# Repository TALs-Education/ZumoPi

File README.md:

# ZumoPi
ZumoPi is a compact robot platform built around the Pololu Zumo chassis and controlled by a Raspberry Pi. This project is used in various educational settings to demonstrate real-world applications of embedded systems, sensor integration, and autonomous control. The slides below cover topics such as configuring embedded hardware, implementing control loops, and developing path-following algorithms. The goal is to give students hands-on experience with building, programming, and testing autonomous robots.

---

---

## Bill of Materials (BOM)

[BOM ZumoPi V02](https://docs.google.com/spreadsheets/d/e/2PACX-1vQxc54kx69_jDI3SzTPj1htnaY2AYKc5NwDaSZi82ZxfzQ_idLNpaMOl1VLD6l9M_Mb7hPjLyrn291Y/pubhtml)

---

## Course Slides

- **[Autonomous Systems Lab](https://docs.google.com/presentation/d/e/2PACX-1vRStIoiYa2XbYNI_D9ZccQSjIIEqi7QFh0CPTO20TWpKoEXQ6jn_6Y2cxPnYvpHpmra1TaAvrsPDCbp/pub?start=false&loop=false&delayms=60000)**
  *Introduction to building and controlling autonomous robots, covering fundamental concepts such as sensor fusion, actuator control, and system integration.*

- **[Embedded](https://docs.google.com/presentation/d/e/2PACX-1vTtC3hYFiazQUpXpRI4Cu9u7xv1cP7oLfKXLLpGbvr99-eDz1KW8hfmtAW4wn4Qjw7GQxjzbYANB0p1/pub?start=false&loop=false&delayms=60000)**  
  *Focus on embedded systems programming, including microcontroller or single-board computer setups, interfacing with hardware, and real-time control considerations.*

- **[PathControl](https://docs.google.com/document/d/e/2PACX-1vTpQWTco3Bi_aDHO9klbxftK4g1yNk0Z4INCxaVdjpg8Rd_K-o5vXg43kFpY49FMV86XIksFvMH8WC9/pub)**  
  *Detailed instructions and theory on path planning and control algorithms, demonstrating how to implement robust path-following routines on the ZumoPi robot.*

- **[PathControl - Python Simulation (PDF)](ZumoPi_V02/EducationalMaterials/ZumoPiV02%20-%20Autonomous%20Systems%20Lab%20-%20Path%20Control%20%28Python%29.pdf)**  
  *Python edition of the Path Control lab: the pre-lab runs in the [Python path control simulator](ZumoPi_V02/Python_Simulation) (GUI with live gain tuning, 2D path and block diagram view) instead of MATLAB/Simulink. Setup instructions are in its [README](ZumoPi_V02/Python_Simulation/README.md).*

- **[ImageProcessing](https://docs.google.com/document/d/e/2PACX-1vQhq_S6ipLvnca8L5krcB6jEdvge32izgGZujL72_1fmICjwPvxk8P4Rqf4jPIfgcK0uPkOjYD1Od2g/pub)**  
  *The Image Processing Lab provides comprehensive guidance and theoretical foundations for practical image processing techniques, demonstrating how to implement vision-based applications on the ZumoPi robot.*

- **[HomeExperiments](https://github.com/TALs-Education/HomeExperiments)**  
  *​The HomeExperiments repository offers students home experiment kits focusing on motor control, Arduino integration, and sensor applications, facilitating hands-on learning of embedded systems concepts.*

---

## Demonstrations

- **[LineFollower 2024](https://youtu.be/RPoe6qCaDEk)**
- **[PathControl 2024](https://youtu.be/oDfgZZBIBZM)**
- **[SumoCompetition 2023](https://youtu.be/UK6Vnh2M9fI)**
- **[Video Teleoperation](https://youtu.be/0YhwoFXWOhQ)**

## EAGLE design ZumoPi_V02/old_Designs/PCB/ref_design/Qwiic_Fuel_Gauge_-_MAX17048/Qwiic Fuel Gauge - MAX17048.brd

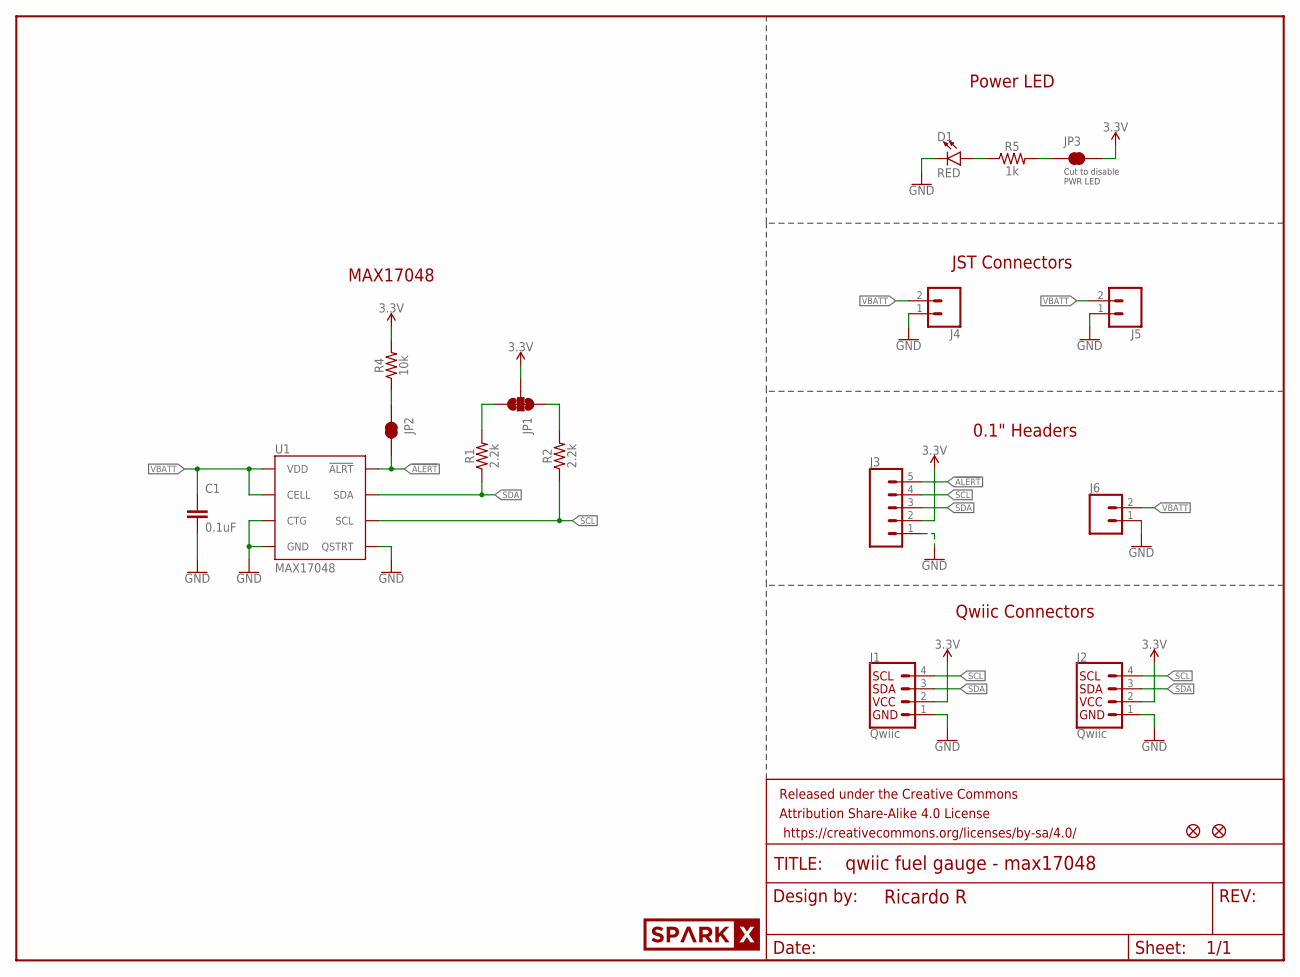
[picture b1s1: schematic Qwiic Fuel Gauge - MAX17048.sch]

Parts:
C1: 0.1uF; 0603
D1: RED; LED-0603
FD1, FD2: FIDUCIAL1X2; FIDUCIAL-1X2
FRAME1: FRAME-LETTERNO_PACKAGE; DUMMY
J1, J2: Qwiic; JST04_1MM_RA
J3: CONN_05NO_SILK; 1X05_NO_SILK
J4, J5: CONN_02-JST-2MM-SMT; JST-2-SMD
J6: CONN_021X02_NO_SILK; 1X02_NO_SILK
JP1: JUMPER-SMT_3_2-NC_TRACE_SILK; SMT-JUMPER_3_2-NC_TRACE_SILK
JP2, JP3: JUMPER-SMT_2_NC_TRACE_SILK; SMT-JUMPER_2_NC_TRACE_SILK
R1, R2: 2.2k; 0603
R4: 10k; 0603
R5: 1k; 0603
U1: MAX17048; DFN-8
U$30: SPARKX-LOGO4; SPARKX-MEDIUM

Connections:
3.3V: J1.2, J2.2, J3.2, JP1.2, JP3.2, R4.2
!ALERT: J3.5, JP2.2, U1.5 (!ALRT)
GND: C1.2, D1.C, J1.1, J2.1, J3.1, J4.1 (2), J5.1 (2), J6.1, U1.1 (CTG), U1.4 (GND), U1.6 (QSTRT), U1.9 (GND)
unnamed: D1.A, R5.1
unnamed: JP1.3, R1.2
unnamed: JP1.1, R2.2
unnamed: JP3.1, R5.2
unnamed: JP2.1, R4.1
SCL: J1.4, J2.4, J3.4, R2.1, U1.7 (SCL)
SDA: J1.3, J2.3, J3.3, R1.1, U1.8 (SDA)
VBATT: C1.1, J4.2 (1), J5.2 (1), J6.2, U1.2 (CELL), U1.3 (VDD)

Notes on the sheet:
Qwiic Connectors
Cut to disable PWR LED
0.1" Headers
JST Connectors
Power LED
MAX17048

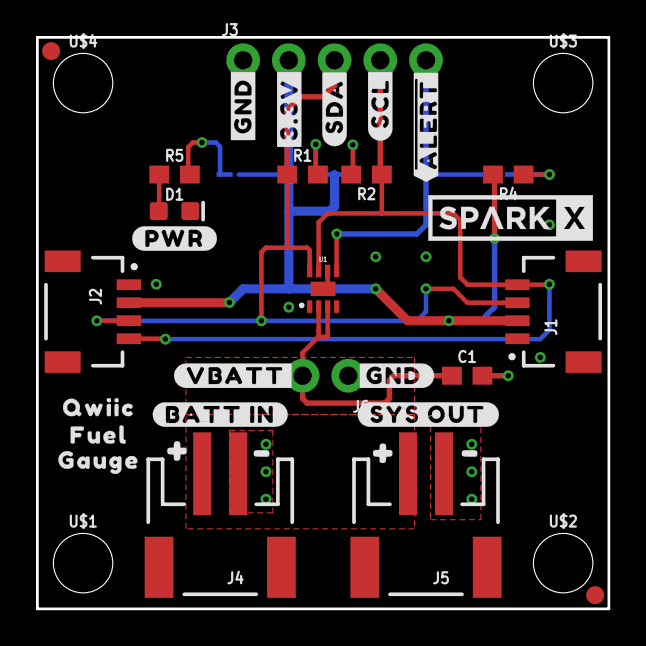
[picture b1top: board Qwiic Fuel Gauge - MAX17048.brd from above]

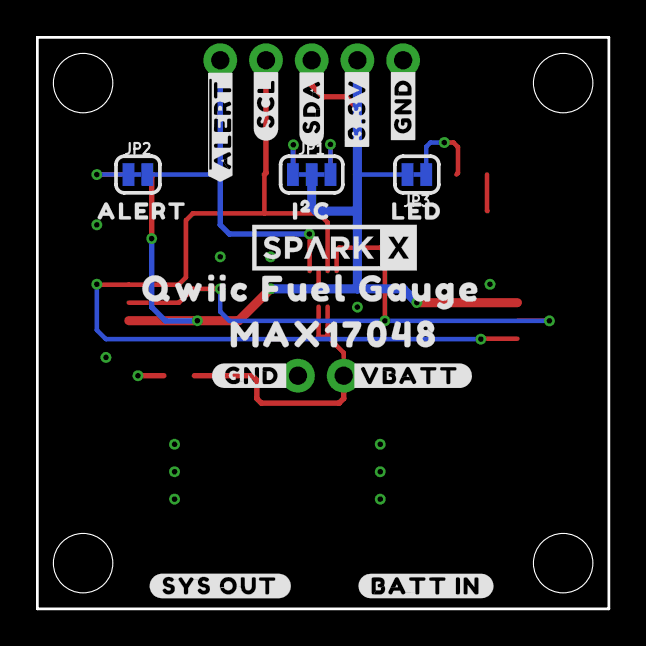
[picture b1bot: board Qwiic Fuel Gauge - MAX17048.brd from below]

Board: 2 copper layers, 31.8 x 31.8 mm, 56 parts (18 on the bottom side), 11 nets.

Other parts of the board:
U$1, U$2, U$3, U$4: STAND-OFF
U$5, U$16: ##ALERT##6
U$6, U$17: #SCL#5
U$7, U$22: #SDA#4
U$8, U$14: #3#3V#1
U$9, U$15: #GND#0
U$10, U$20: #BATT_IN#8
U$11, U$37: #SYS_OUT#0
U$12: #VBATT#10
U$13: #GND#7
U$18: #GND#1708416
U$19: #VBATT#1708415
U$21: SPARKX-LOGO4; SPARKX-MEDIUM
U$23: MAX170481
U$24: FUEL1
U$25: ALERT1708413
U$26: #PWR#1708412
U$27: QWIIC_FUEL_GAUGE0
U$28: I�C0
U$29: LED1
U$31: GAUGE2
U$32: QWIIC0
U$33, U$34: #0
U$35, U$36: #1

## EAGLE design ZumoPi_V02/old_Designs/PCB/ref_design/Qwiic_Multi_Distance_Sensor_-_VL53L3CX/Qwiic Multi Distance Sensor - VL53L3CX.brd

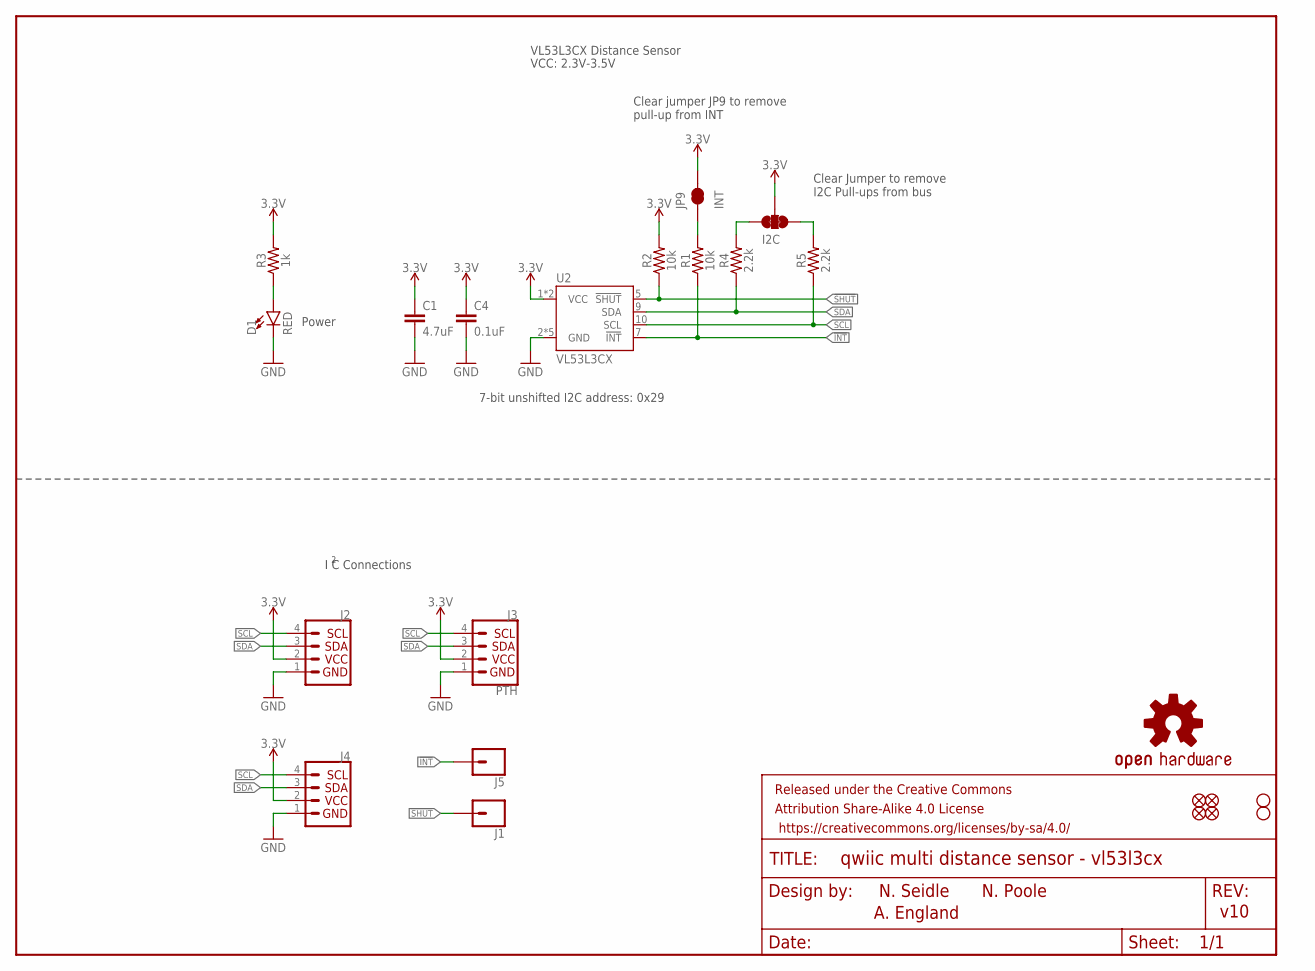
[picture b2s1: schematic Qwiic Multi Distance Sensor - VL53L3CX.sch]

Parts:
C1: 4.7uF; 0603
C4: 0.1uF; 0603
D1: RED; LED-0603
FRAME1: FRAME-LETTERNO_PACKAGE; DUMMY
I2C: JUMPER-SMT_3_2-NC_TRACE_SILK; SMT-JUMPER_3_2-NC_TRACE_SILK
J1, J5: CONN_01PTH_NO_SILK_YES_STOP; 1X01_NO_SILK
J2, J4: QWIIC_CONNECTORJS-1MM; 1X04_1MM_RA
J3: PTH; 1X04_NO_SILK
JP1, JP2, JP5, JP6: FIDUCIALUFIDUCIAL; MICRO-FIDUCIAL
JP3, JP4: STAND-OFF
JP9: INT; PAD-JUMPER-2-NC_BY_TRACE_YES_SILK
LOGO1: OSHW-LOGOMINI; OSHW-LOGO-MINI
R1, R2: 10k; 0603
R3: 1k; 0603
R4, R5: 2.2k; 0603
U2: VL53L3CX; VL53L1X

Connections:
3.3V: C1.1, C4.1, I2C.2, J2.2, J3.2 (VCC), J4.2, JP9.2, R2.2, R3.2, U2.1 (VCC), U2.11 (VCC)
!INT: J5.1, R1.1, U2.7 (!INT)
!SHUT: J1.1, R2.1, U2.5 (!SHUT)
GND: C1.2, C4.2, D1.C, J2.1, J3.1 (GND), J4.1, U2.2 (GND), U2.3 (GND), U2.4 (GND), U2.6 (GND), U2.12 (GND)
unnamed: I2C.1, R5.2
unnamed: I2C.3, R4.2
unnamed: D1.A, R3.1
unnamed: JP9.1, R1.2
SCL: J2.4, J3.4 (SCL), J4.4, R5.1, U2.10 (SCL)
SDA: J2.3, J3.3 (SDA), J4.3, R4.1, U2.9 (SDA)

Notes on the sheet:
N. Seidle
v10
7-bit unshifted I2C address: 0x29
Clear Jumper to remove I2C Pull-ups from bus
Clear jumper JP9 to remove pull-up from INT
Power
A. England
I C Connections
VL53L3CX Distance Sensor
VCC: 2.3V-3.5V
N. Poole

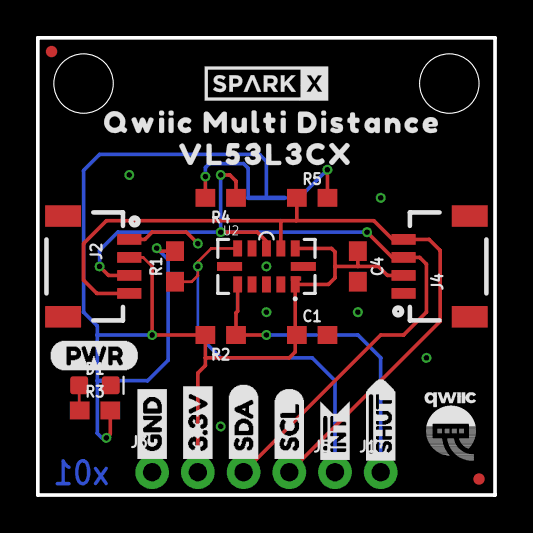
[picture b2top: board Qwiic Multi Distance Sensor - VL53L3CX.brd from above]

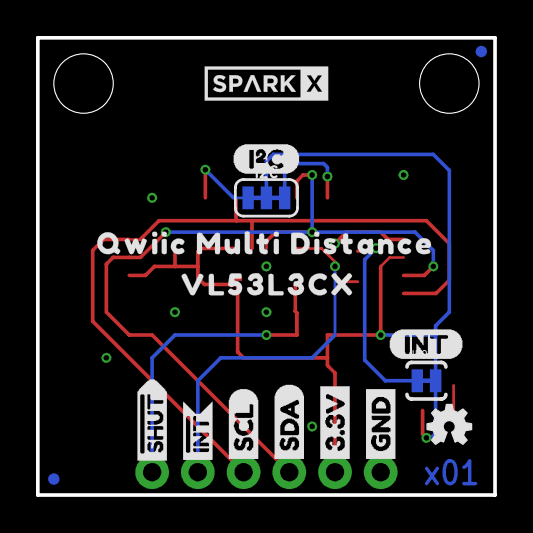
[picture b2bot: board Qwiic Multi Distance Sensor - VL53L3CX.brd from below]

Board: 2 copper layers, 25.4 x 25.4 mm, 46 parts (16 on the bottom side), 10 nets.

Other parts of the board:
U$1, U$16: VL53L3CX0
U$2, U$15: QWIIC_MULTI_DISTANCE1
U$3, U$22: GND1
U$4, U$21: 3#3V2
U$5, U$27: SDA8
U$6, U$26: SCL9
U$7, U$14: INT#-[<
U$8, U$9: #SHUT15
U$10: (PWR)
U$11: (I_SUPER2_C)
U$12: (INT)
U$13: QWIIC-LOGO-SMALL
U$17, U$18: SPARKX-SMALL

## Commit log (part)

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2023-03-20 simulation
2023-04-18 updated simulation
2023-04-20 codes for testing
2023-04-23 joystick
2023-05-17 zumo simulation
2023-06-28 pathConbtriol library
2023-10-15 update names
2023-10-16 simulations update
2024-02-19 ros2 development
2024-02-19 ros2 mocap example
2024-11-26 zumoPi V02
2025-01-27 updates ZumoPi_V02
2025-01-28 added support to 2025 raspbian
2025-02-05 uart examples
2025-02-17 barcode detection
2025-02-17 updates to the detection code
2025-02-24 arduino examples update
2025-02-25 example codes
2025-02-25 additional examples
2025-02-25 updated image detection example
2025-02-26 updated examples
2025-02-27 updates to examples
2025-03-09 path example
2025-03-11 images
2025-03-12 Image Processing
2025-03-17 development
2025-03-18 python examples
2025-03-18 documentation
2025-04-08 Stop condition: if at last point and within stopDistance or if last point is behind.
2025-06-05 update stop condition
2025-11-20 Assembly Images
2025-12-15 zumo updates
2025-12-15 documentation update
2026-02-22 configurations
2026-05-14 traffic cone

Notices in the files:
parts and their libraries:
SparkFun-Capacitors: Licensing: Creative Commons ShareAlike 4.0 International - https://creativecommons.org/licenses/by-sa/4.0
SparkFun-Aesthetics: Released under the Creative Commons Attribution Share-Alike 4.0 License
SparkFun-Aesthetics: https://creativecommons.org/licenses/by-sa/4.0
